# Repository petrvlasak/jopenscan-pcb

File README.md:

# [JOpenScan](https://github.com/petrvlasak/jopenscan?tab=readme-ov-file#jopenscan) - Pi Shield and Ringlight PCBs

These PCBs are compatible with the original [OpenScan](https://openscan.eu/) DIY 3D Scanner [firmware](https://openscan-org.github.io/OpenScan-Doc/firmware/setup/). They contain some improvements:

- Pi Shield
  - Proper current limiting resistors for MOSFETs in Ringlight control
  - Software shutdown of stepper motors (available only in [JOpenScan firmware](https://github.com/petrvlasak/jopenscan))
- Ringlight
  - Removed unnecessary current limiting resistors

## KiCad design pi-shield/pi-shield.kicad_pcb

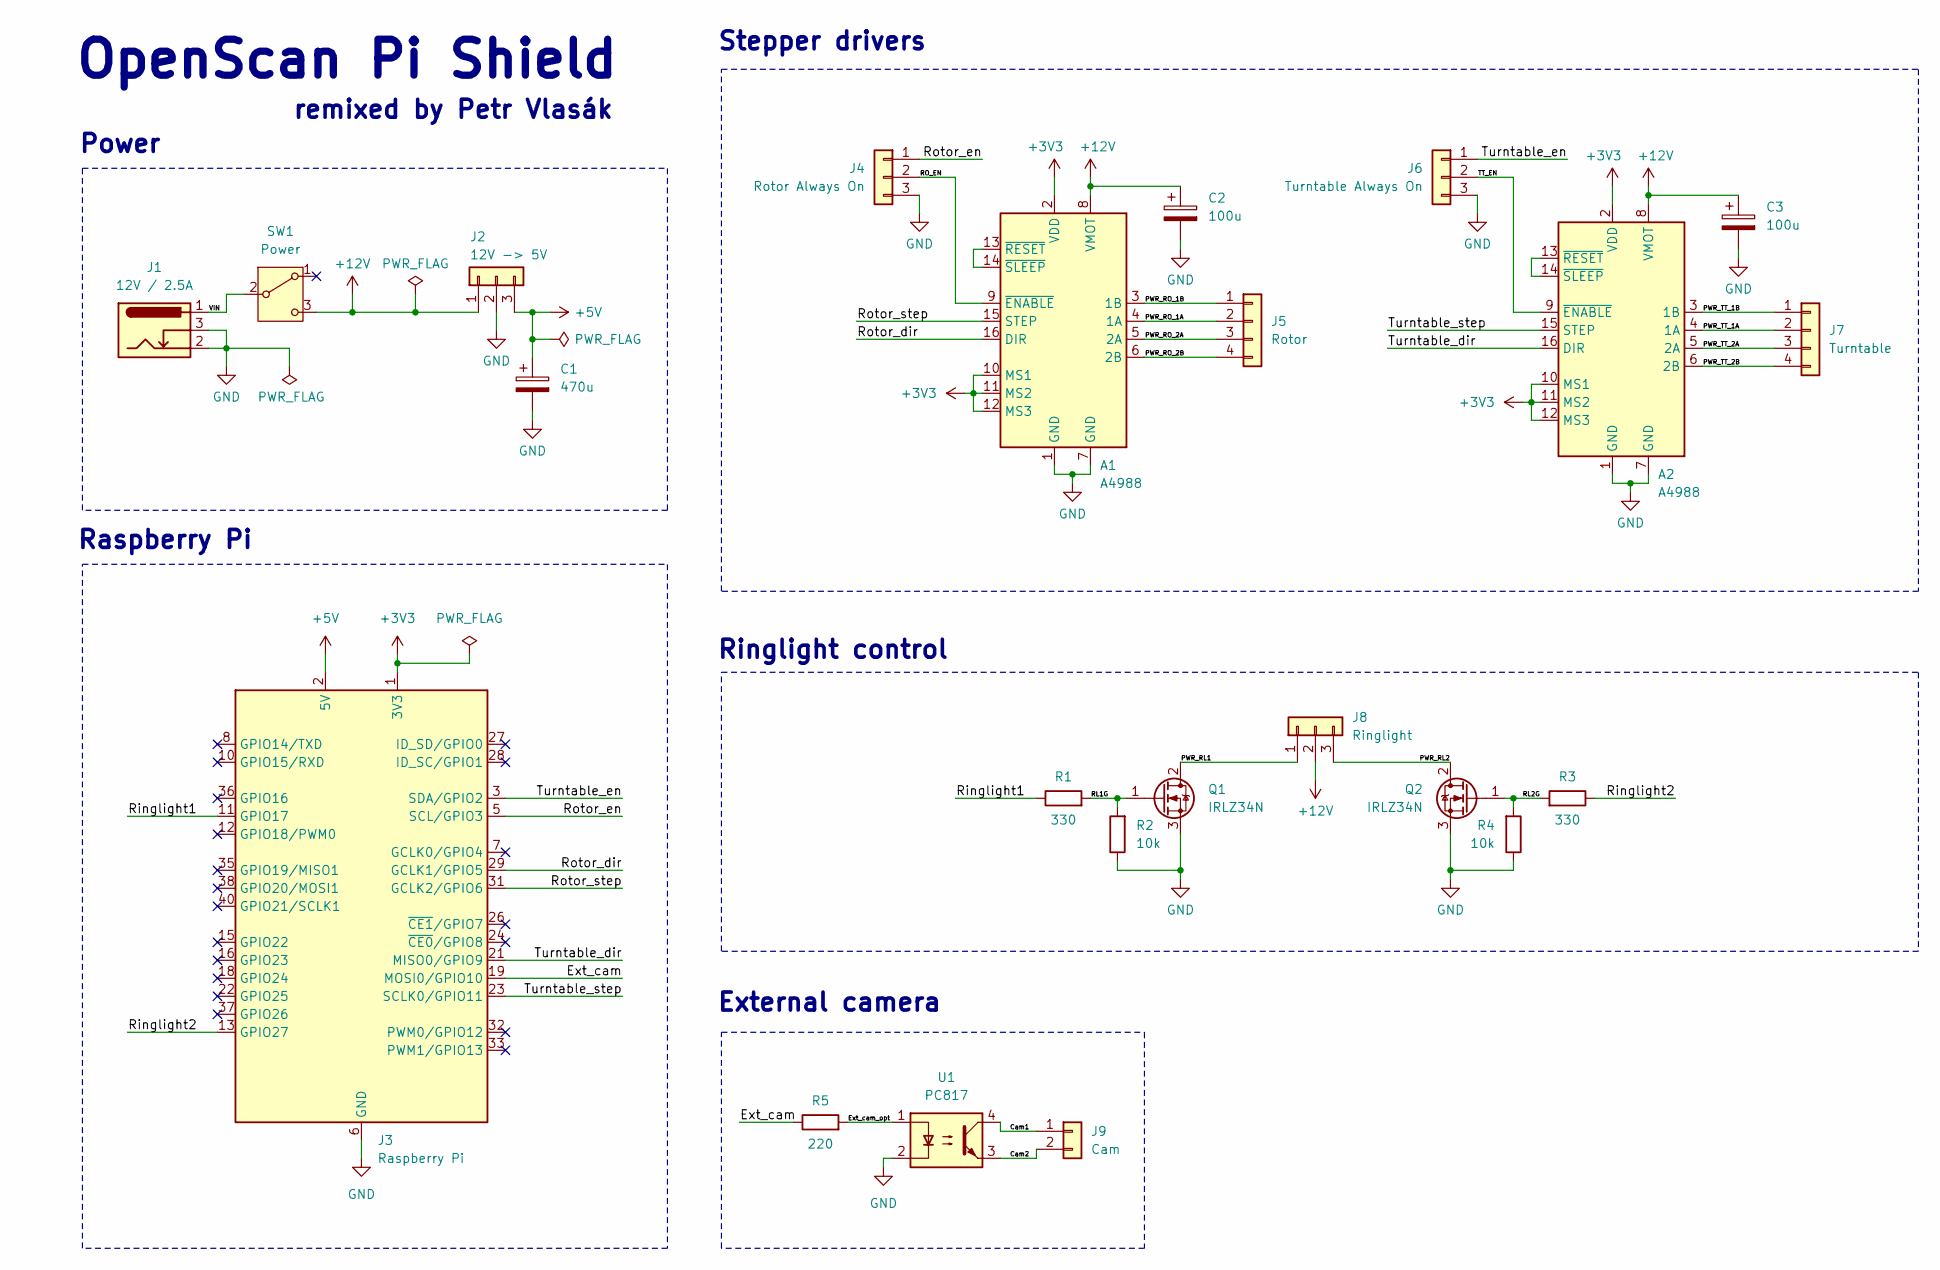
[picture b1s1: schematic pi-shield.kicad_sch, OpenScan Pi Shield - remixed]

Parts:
A1, A2: A4988
C1: 470u; CP_Radial_D6.3mm_P2.50mm
C2, C3: 100u; CP_Radial_D6.3mm_P2.50mm
J1: 12V / 2.5A; BarrelJack_GCT_DCJ200-10-A_Horizontal
J2: 12V -> 5V; PinHeader_1x03_P2.54mm_Vertical
J3: Raspberry Pi; PinSocket_2x20_P2.54mm_Vertical
J4: Rotor Always On; PinHeader_1x03_P2.54mm_Vertical
J5: Rotor; PinHeader_1x04_P2.54mm_Vertical
J6: Turntable Always On; PinHeader_1x03_P2.54mm_Vertical
J7: Turntable; PinHeader_1x04_P2.54mm_Vertical
J8: Ringlight; JST_XH_B3B-XH-A_1x03_P2.50mm_Vertical
J9: Cam; PinSocket_1x02_P2.54mm_Vertical
Q1, Q2: IRLZ34N; TO-220-3_Horizontal_TabDown
R1, R3: 330; R_Axial_DIN0207_L6.3mm_D2.5mm_P10.16mm_Horizontal
R2, R4: 10k; R_Axial_DIN0207_L6.3mm_D2.5mm_P10.16mm_Horizontal
R5: 220; R_Axial_DIN0207_L6.3mm_D2.5mm_P10.16mm_Horizontal
SW1: Power; SW_SPDT_CANAL_ELECTRONIC_SL19-121
U1: PC817; DIP-4_W7.62mm

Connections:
+3V3: A1.2 (VDD), A1.10 (MS1), A1.11 (MS2), A1.12 (MS3), A2.2 (VDD), A2.10 (MS1), A2.11 (MS2), A2.12 (MS3), J3.1 (3V3), J3.17 (3V3)
+5V: C1.1, J2.3, J3.2 (5V), J3.4 (5V)
+12V: A1.8 (VMOT), A2.8 (VMOT), C2.1, C3.1, J2.1, J8.2, SW1.3 (C)
/Cam1: J9.1, U1.4
/Cam2: J9.2, U1.3
/Ext_cam: J3.19 (MOSI0/GPIO10), R5.1
/Ext_cam_opt: R5.2, U1.1
/PWR_RL1: J8.1, Q1.2 (D)
/PWR_RL2: J8.3, Q2.2 (D)
/PWR_RO_1A: A1.4 (1A), J5.2
/PWR_RO_1B: A1.3 (1B), J5.1
/PWR_RO_2A: A1.5 (2A), J5.3
/PWR_RO_2B: A1.6 (2B), J5.4
/PWR_TT_1A: A2.4 (1A), J7.2
/PWR_TT_1B: A2.3 (1B), J7.1
/PWR_TT_2A: A2.5 (2A), J7.3
/PWR_TT_2B: A2.6 (2B), J7.4
/RL1G: Q1.1 (G), R1.2, R2.2
/RL2G: Q2.1 (G), R3.2, R4.2
/RO_EN: A1.9 (~ENABLE), J4.2
/Ringlight1: J3.11 (GPIO17), R1.1
/Ringlight2: J3.13 (GPIO27), R3.1
/Rotor_dir: A1.16 (DIR), J3.29 (GCLK1/GPIO5)
/Rotor_en: J3.5 (SCL/GPIO3), J4.1
/Rotor_step: A1.15 (STEP), J3.31 (GCLK2/GPIO6)
/TT_EN: A2.9 (~ENABLE), J6.2
/Turntable_dir: A2.16 (DIR), J3.21 (MISO0/GPIO9)
/Turntable_en: J3.3 (SDA/GPIO2), J6.1
/Turntable_step: A2.15 (STEP), J3.23 (SCLK0/GPIO11)
/VIN: J1.1, SW1.2 (B)
GND: A1.1 (GND), A1.7 (GND), A2.1 (GND), A2.7 (GND), C1.2, C2.2, C3.2, J1.2, J1.3, J2.2, J3.6 (GND), J3.9 (GND), J3.14 (GND), J3.20 (GND), J3.25 (GND), J3.30 (GND), J3.34 (GND), J3.39 (GND), J4.3, J6.3, Q1.3 (S), Q2.3 (S), R2.1, R4.1, U1.2
unnamed: A1.13 (~RESET), A1.14 (~SLEEP)
unnamed: A2.13 (~RESET), A2.14 (~SLEEP)

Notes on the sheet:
External camera
Power
remixed by Petr Vlasák
Ringlight control
OpenScan Pi Shield
Raspberry Pi
Stepper drivers

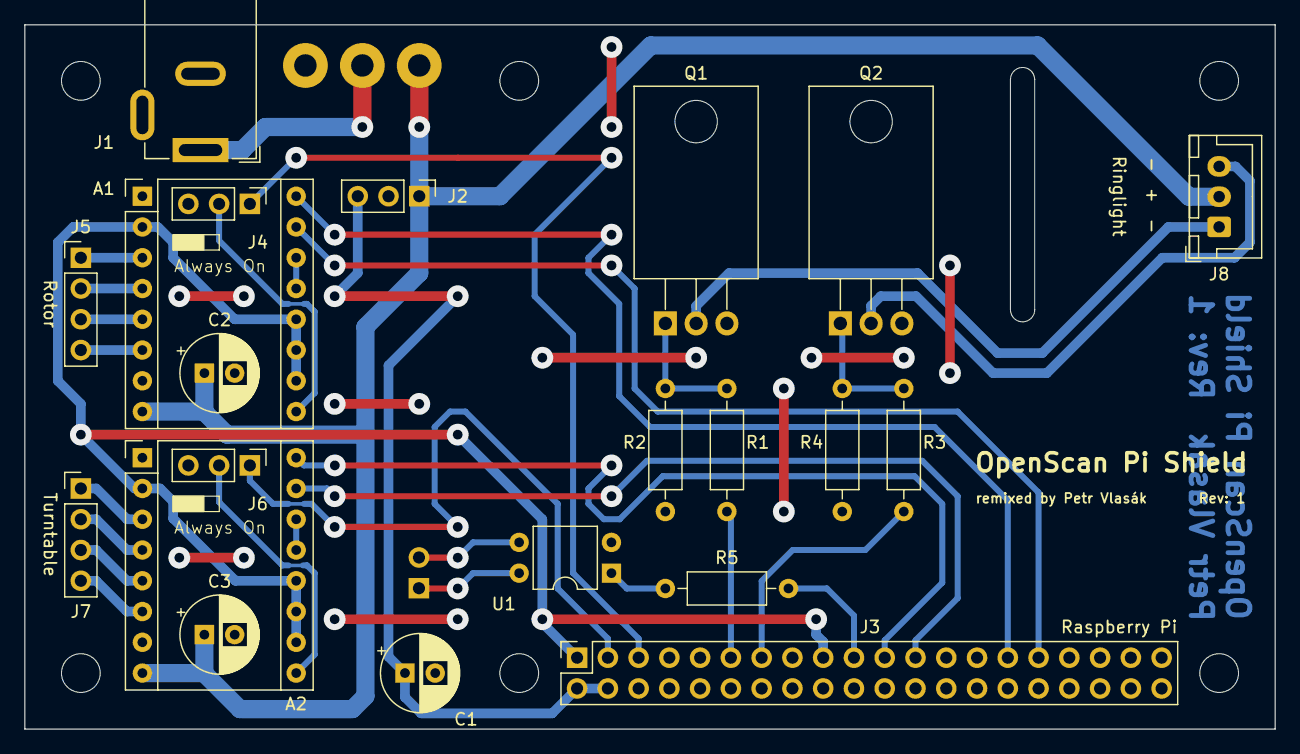
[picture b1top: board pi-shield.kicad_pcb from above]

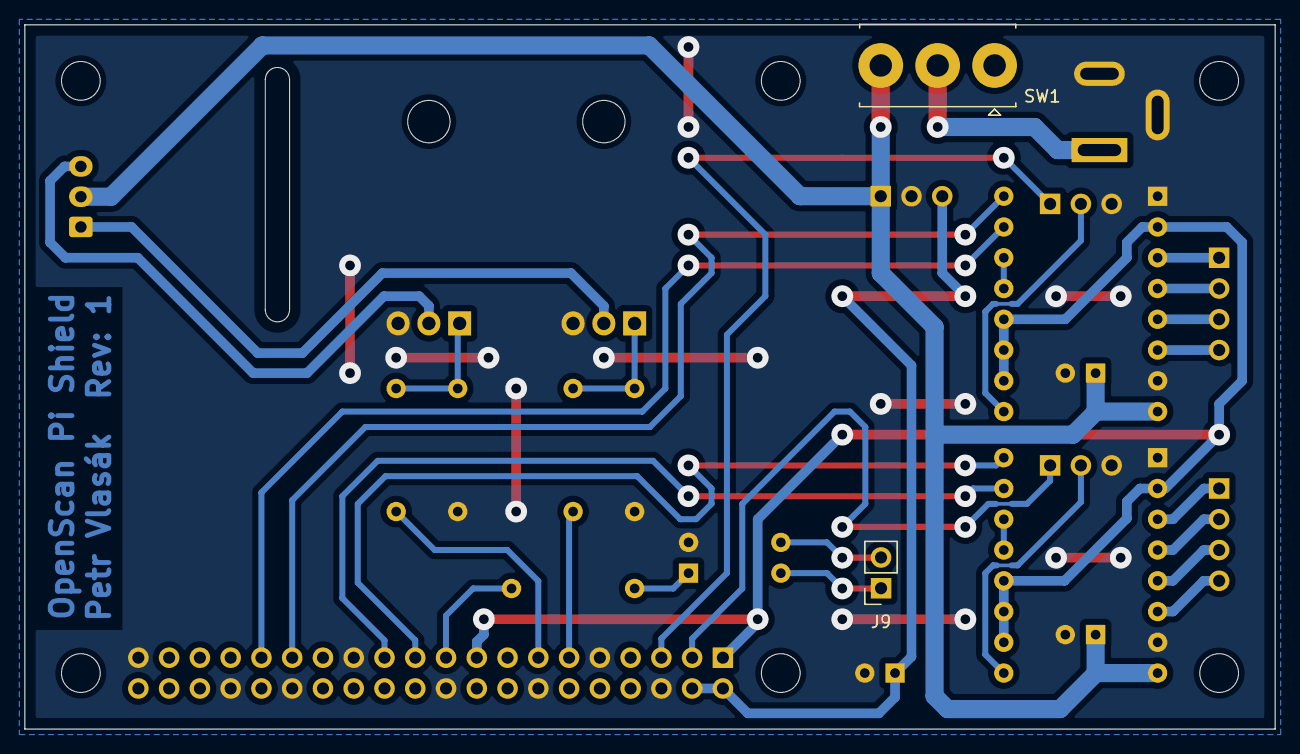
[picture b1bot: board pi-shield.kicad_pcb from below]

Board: 2 copper layers, 103.2 x 58.1 mm, 23 parts (2 on the bottom side), 33 nets.

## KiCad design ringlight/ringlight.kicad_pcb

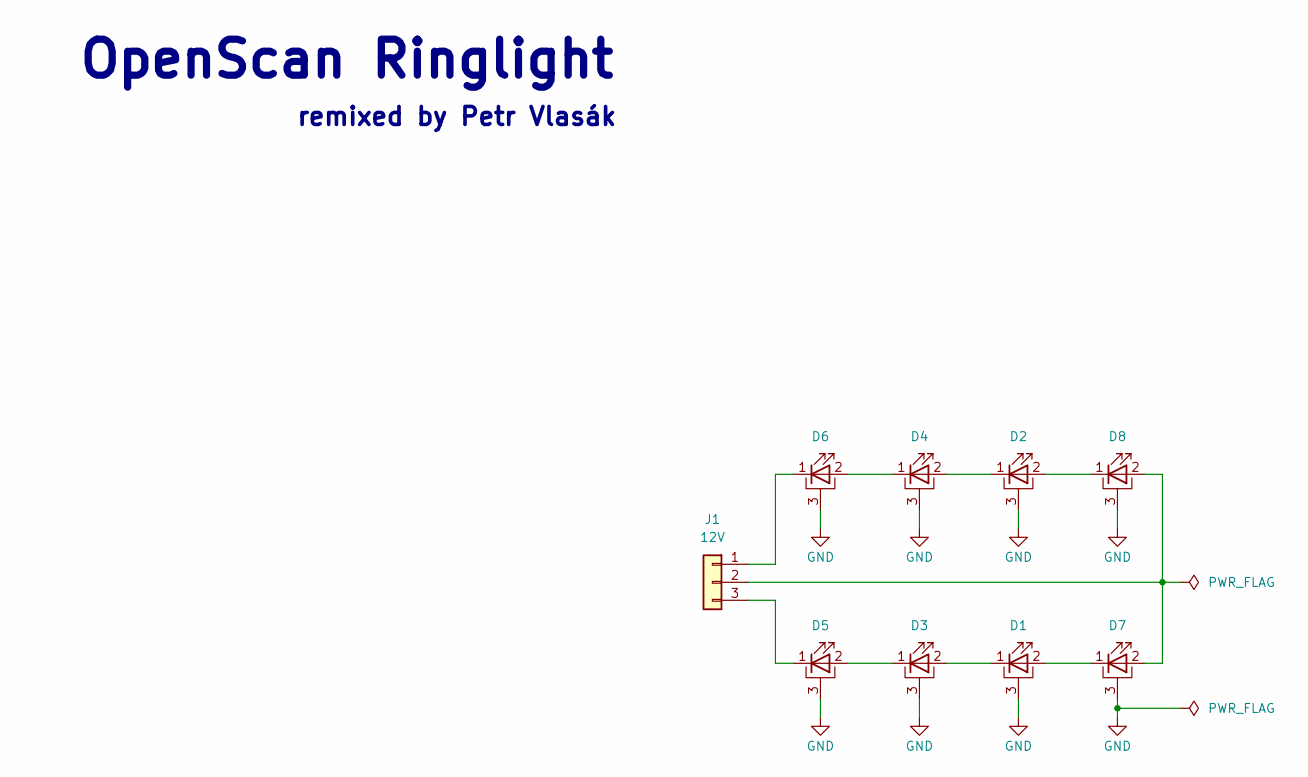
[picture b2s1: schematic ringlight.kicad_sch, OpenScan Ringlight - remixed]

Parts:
D1, D2, D3, D4, D5, D6, D7, D8: LED_Pad; LED_1W_3W_R8
J1: 12V; SolderWire-0.5sqmm_1x03_P4.8mm_D0.9mm_OD2.3mm

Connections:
GND: D1.3 (PAD), D2.3 (PAD), D3.3 (PAD), D4.3 (PAD), D5.3 (PAD), D6.3 (PAD), D7.3 (PAD), D8.3 (PAD)
unnamed: D1.2 (A), D7.1 (K)
unnamed: D1.1 (K), D3.2 (A)
unnamed: D2.2 (A), D8.1 (K)
unnamed: D2.1 (K), D4.2 (A)
unnamed: D3.1 (K), D5.2 (A)
unnamed: D4.1 (K), D6.2 (A)
unnamed: D5.1 (K), J1.3
unnamed: D6.1 (K), J1.1
unnamed: D7.2 (A), D8.2 (A), J1.2

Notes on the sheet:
remixed by Petr Vlasák
OpenScan Ringlight

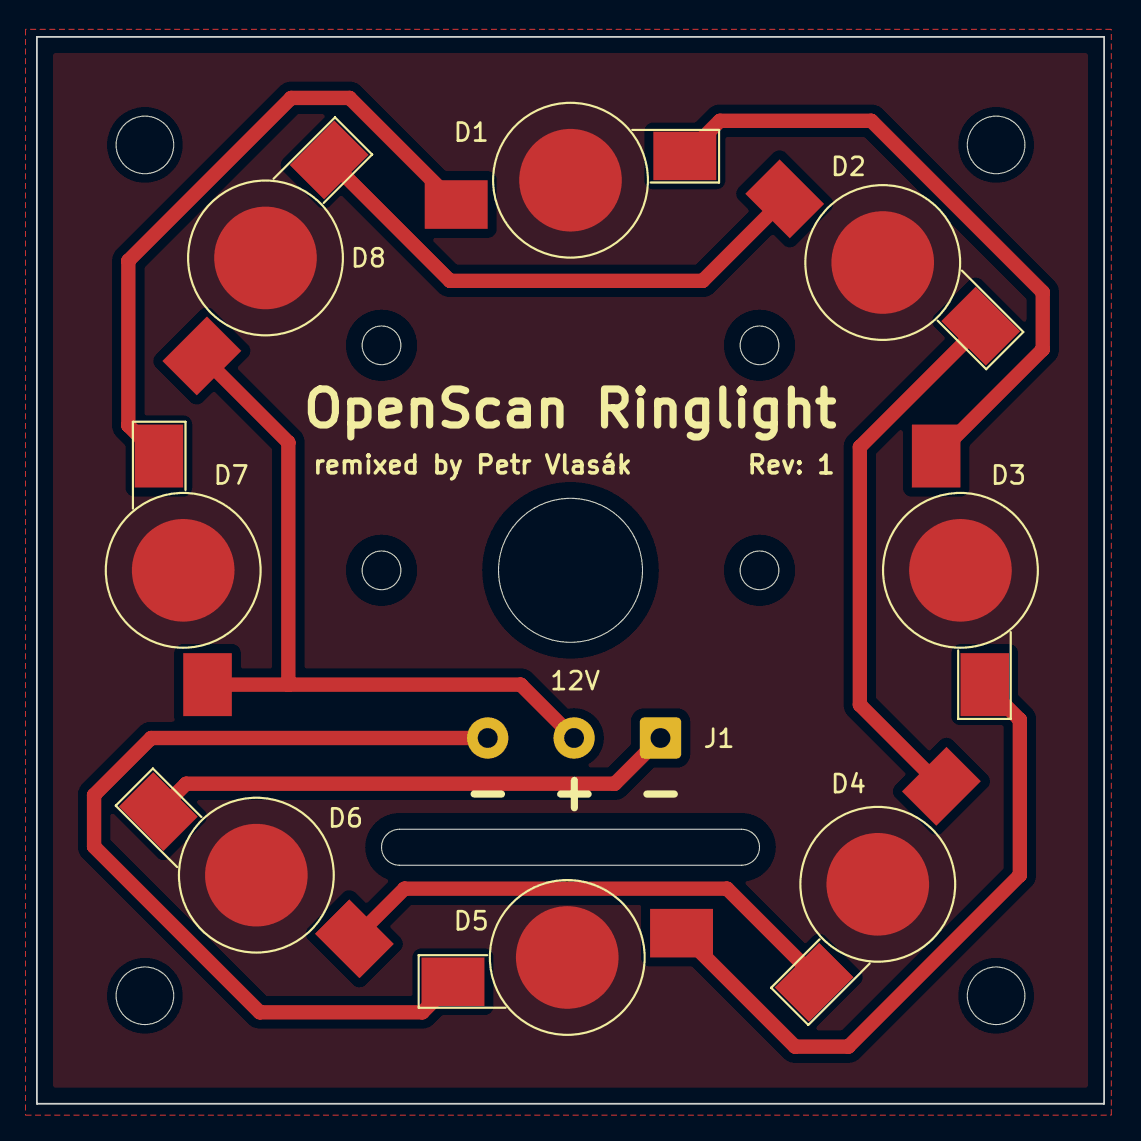
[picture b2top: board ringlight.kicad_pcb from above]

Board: 2 copper layers, 59.3 x 59.3 mm, 9 parts (0 on the bottom side), 10 nets.

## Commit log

2025-07-07 License file
2025-07-07 Readme file
2025-07-08 Added photo to the readme file
2025-07-10 Small description improvement

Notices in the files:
pi-shield/pi-shield.kicad_sch:
GPL-3.0 license
